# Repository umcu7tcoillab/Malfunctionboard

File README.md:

# Malfunctionboard

## About us
This design has been made by the coil-lab of the High Field MRI Group of the UMC Utrecht in the Netherlands, where we make hardware to support our researchers. We are part of a research group which means we feel the need to open up some of our designs to whomever can make use of it, to further the research of MRI applications.

## The design
This project contains a Malfunctionboard made for our 7T Philips Achieva MRI system. It has been tested inside the magnetic field of the 7T MRI. 

The Malfunctionboard is used to check the state of the PIN-diodes of the attachted coil. Between 1 and 3 diodes (0.4-2.6V) passes the test, otherwise the malfunctionline will not be pulled high.

The design and subsequent drawing has been done in Kicad 5.1.5.

## Download
Gerber and BOM production files for the latest _field tested_ version of the PCB can be found in the 'Releases' page, or by following [this link](https://github.com/umcu7tcoillab/Malfunctionboard/releases/latest). 
You can also make your own production files by downloading the Kicad project and generating them, but these are not guaranteed to have been field tested.

## Images
**3D Image**

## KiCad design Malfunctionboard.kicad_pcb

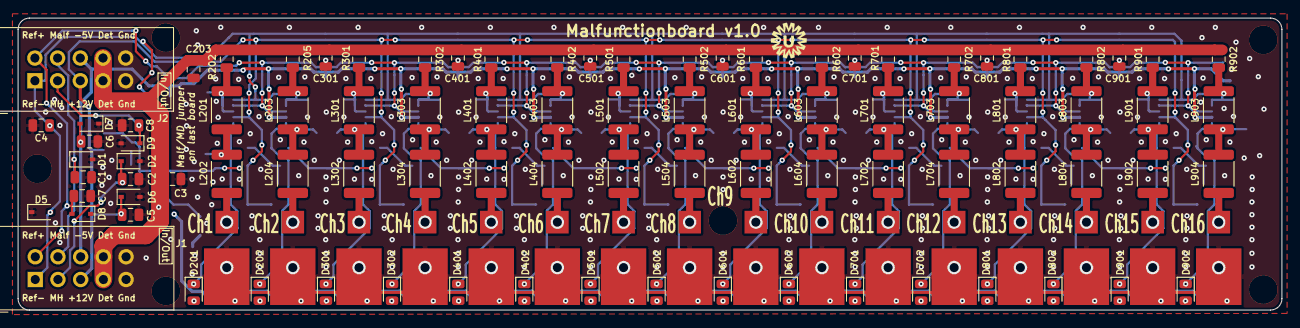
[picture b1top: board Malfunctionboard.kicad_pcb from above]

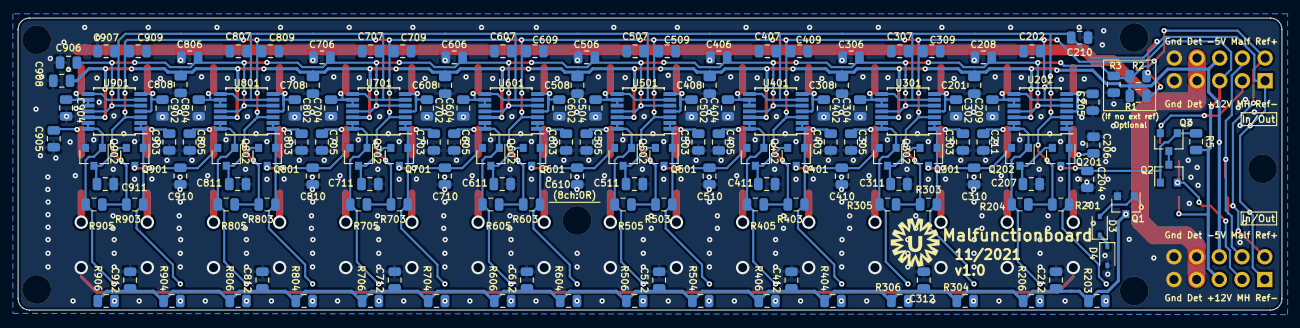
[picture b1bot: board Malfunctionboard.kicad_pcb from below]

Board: 2 copper layers, 141.4 x 32.7 mm, 265 parts (154 on the bottom side), 108 nets.

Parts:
C1, C2, C3, C4, C7, C8, C203, C204, C205, C206, C207, C208, C209, C210, C211, C301, C302, C303, C304, C305, C306, C307, C310, C311, C401, C402, C403, C404, C405, C406, C407, C410, C411, C501, C502, C503, C504, C505, C506, C507, C510, C511, C601, C602, C603, C604, C605, C606, C607, C610, C611, C701, C702, C703, C704, C705, C706, C707, C710, C711, C801, C802, C803, C804, C805, C806, C807, C810, C811, C901, C902, C903, C904, C905, C906, C907, C910, C911: 470pF; C_0805_2012Metric
C5, C6, C201, C202, C212, C308, C309, C312, C408, C409, C412, C508, C509, C512, C608, C609, C612, C708, C709, C712, C808, C809, C812, C908, C909, C912: 10n; C_0805_2012Metric
D1, D2, D6, D9: 15V; D_SOD-323
D3, D5, D7, D8: 5.4V; D_SOD-323
D4: 12V; D_SOD-323
D201, D202, D301, D302, D401, D402, D501, D502, D601, D602, D701, D702, D801, D802, D901, D902: LED; LED_0805_2012Metric
H1, H3, H4, H5, H6, H7: MH_Pad; MountingHole_3.2mm_M3_plated
J1, J2: In/out; IDC-Header_2x05_P2.54mm_Vertical
J201, J202, J301, J302, J401, J402, J501, J502, J601, J602, J701, J702, J801, J802, J901, J902: Conn_Coaxial; Solder straight thin coax cable
L201, L202, L203, L204, L301, L302, L303, L304, L401, L402, L403, L404, L501, L502, L503, L504, L601, L602, L603, L604, L701, L702, L703, L704, L801, L802, L803, L804, L901, L902, L903, L904: 1u; L_1812_4532Metric
Q1, Q2, Q3: RSC002P03T316; SOT-23
Q201, Q202, Q301, Q302, Q401, Q402, Q501, Q502, Q601, Q602, Q701, Q702, Q801, Q802, Q901, Q902: NTR5103NT1G; SOT-23
R1: R_Ref-; R_0805_2012Metric
R2: R_Ref; R_0805_2012Metric
R3: R_Ref+; R_0805_2012Metric
R5: 1k; R_0805_2012Metric
R201, R204, R303, R305, R403, R405, R503, R505, R603, R605, R703, R705, R803, R805, R903, R905: 100k; R_0805_2012Metric
R202, R205, R301, R302, R401, R402, R501, R502, R601, R602, R701, R702, R801, R802, R901, R902: 150R; R_0805_2012Metric
R203, R206, R304, R306, R404, R406, R504, R506, R604, R606, R704, R706, R804, R806, R904, R906: 10k; R_0805_2012Metric
SYM1: SYM_Magnet_Small; UMC_logo_small
U201, U301, U401, U501, U601, U701, U801, U901: LM339PW; TSSOP-14_4.4x5mm_P0.65mm

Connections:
+12V: C5.1, C202.2, C309.2, C409.2, C509.2, C609.2, C709.2, C809.2, C909.2, D6.1, J1.5, J2.5, R5.1, R201.1, R204.1, R303.1, R305.1, R403.1, R405.1, R503.1, R505.1, R603.1, R605.1, R703.1, R705.1, R803.1, R805.1, R903.1, R905.1, U201.3, U301.3, U401.3, U501.3, U601.3, U701.3, U801.3, U901.3
-5V: C6.1, C201.2, C308.2, C408.2, C508.2, C608.2, C708.2, C808.2, C908.2, D7.2, J1.6, J2.6, R1.1, U201.12, U301.12, U401.12, U501.12, U601.12, U701.12, U801.12, U901.12
/MH_1: C2.2, D2.1, J1.3, Q2.2
/MH_2: C8.2, D9.1, J2.3, Q3.2
/Malf: C1.2, D1.1, J1.4, J2.4
/Ref+: C7.2, C208.2, C306.2, C406.2, C506.2, C606.2, C706.2, C806.2, C906.2, D8.2, J1.2, J2.2, R2.2, R3.1, U201.5, U201.11, U301.5, U301.11, U401.5, U401.11, U501.5, U501.11, U601.5, U601.11, U701.5, U701.11, U801.5, U801.11, U901.5, U901.11
/Ref-: C4.2, C210.2, C307.2, C407.2, C507.2, C607.2, C707.2, C807.2, C907.2, D5.2, J1.1, J2.1, R1.2, R2.1, U201.6, U201.8, U301.6, U301.8, U401.6, U401.8, U501.6, U501.8, U601.6, U601.8, U701.6, U701.8, U801.6, U801.8, U901.6, U901.8
/V_detune: C3.2, C203.2, C301.2, C401.2, C501.2, C601.2, C701.2, C801.2, C901.2, D3.2, J1.7, J1.8, J2.7, J2.8, Q1.1, R202.1, R205.1, R301.1, R302.1, R401.1, R402.1, R501.1, R502.1, R601.1, R602.1, R701.1, R702.1, R801.1, R802.1, R901.1, R902.1
/sheet5DD8DCB3/LED_GND: C212.1, C312.1, C412.1, C512.1, C612.1, C712.1, C812.1, C912.1, Q1.3, R203.2, R206.2, R304.2, R306.2, R404.2, R406.2, R504.2, R506.2, R604.2, R606.2, R704.2, R706.2, R804.2, R806.2, R904.2, R906.2
/sheet5DD8DCB3/Malf: C310.2, Q202.2, Q301.3
/sheet5DD8DCB3/Malf_in: C204.2, Q2.1, Q3.1, Q201.3, R5.2
/sheet5DE59C6C/Malf: C410.2, Q302.2, Q401.3
/sheet5DF0CFC9/Malf: C510.2, Q402.2, Q501.3
/sheet5DF0CFCA/Malf: C610.2, Q502.2, Q601.3
/sheet5DF270F0/Malf: C710.2, Q602.2, Q701.3
/sheet5DF270F1/Malf: C810.2, Q702.2, Q801.3
/sheet5DF3552B/Malf: C910.2, Q802.2, Q901.3
GND: C1.1, C2.1, C3.1, C4.1, C5.2, C6.2, C7.1, C8.1, C201.1, C202.1, C203.1, C204.1, C205.1, C206.1, C207.2, C208.1, C209.1, C210.1, C211.1, C212.2, C301.1, C302.1, C303.1, C304.1, C305.1, C306.1, C307.1, C308.1, C309.1, C310.1, C311.2, C312.2, C401.1, C402.1, C403.1, C404.1, C405.1, C406.1, C407.1, C408.1, C409.1, C410.1, C411.2, C412.2, C501.1, C502.1, C503.1, C504.1, C505.1, C506.1, C507.1, C508.1, C509.1, C510.1, C511.2, C512.2, C601.1, C602.1, C603.1, C604.1, C605.1, C606.1, C607.1, C608.1, C609.1, C610.1, C611.2, C612.2, C701.1, C702.1, C703.1, C704.1, C705.1, C706.1, C707.1, C708.1, C709.1, C710.1, C711.2, C712.2, C801.1, C802.1, C803.1, C804.1, C805.1, C806.1, C807.1, C808.1, C809.1, C810.1, C811.2, C812.2, C901.1, C902.1, C903.1, C904.1, C905.1, C906.1, C907.1, C908.1, C909.1, C910.1, C911.2, C912.2, D1.2, D2.2, D4.2, D5.1, D6.2, D7.1, D8.1, D9.2, H1.1, H3.1, H4.1, H5.1, H6.1, H7.1, J1.9, J1.10, J2.9, J2.10, J201.2, J202.2, J301.2, J302.2, J401.2, J402.2, J501.2, J502.2, J601.2, J602.2, J701.2, J702.2, J801.2, J802.2, J901.2, J902.2, Q1.2, Q902.2, R3.2
unnamed: C205.2, L201.2, R202.2, U201.4, U201.7
unnamed: C206.2, L201.1, L202.2
unnamed: C207.1, Q201.2, Q202.3
unnamed: C209.2, L203.2, R205.2, U201.9, U201.10
unnamed: C211.2, L203.1, L204.2
unnamed: C302.2, L301.2, R301.2, U301.4, U301.7
unnamed: C303.2, L301.1, L302.2
unnamed: C304.2, L303.2, R302.2, U301.9, U301.10
unnamed: C305.2, L303.1, L304.2
unnamed: C311.1, Q301.2, Q302.3
unnamed: C402.2, L401.2, R401.2, U401.4, U401.7
unnamed: C403.2, L401.1, L402.2
unnamed: C404.2, L403.2, R402.2, U401.9, U401.10
unnamed: C405.2, L403.1, L404.2
unnamed: C411.1, Q401.2, Q402.3
unnamed: C502.2, L501.2, R501.2, U501.4, U501.7
unnamed: C503.2, L501.1, L502.2
unnamed: C504.2, L503.2, R502.2, U501.9, U501.10
unnamed: C505.2, L503.1, L504.2
unnamed: C511.1, Q501.2, Q502.3
unnamed: C602.2, L601.2, R601.2, U601.4, U601.7
unnamed: C603.2, L601.1, L602.2
unnamed: C604.2, L603.2, R602.2, U601.9, U601.10
unnamed: C605.2, L603.1, L604.2
unnamed: C611.1, Q601.2, Q602.3
unnamed: C702.2, L701.2, R701.2, U701.4, U701.7
unnamed: C703.2, L701.1, L702.2
unnamed: C704.2, L703.2, R702.2, U701.9, U701.10
unnamed: C705.2, L703.1, L704.2
unnamed: C711.1, Q701.2, Q702.3
unnamed: C802.2, L801.2, R801.2, U801.4, U801.7
unnamed: C803.2, L801.1, L802.2
unnamed: C804.2, L803.2, R802.2, U801.9, U801.10
unnamed: C805.2, L803.1, L804.2
unnamed: C811.1, Q801.2, Q802.3
unnamed: C902.2, L901.2, R901.2, U901.4, U901.7
unnamed: C903.2, L901.1, L902.2
unnamed: C904.2, L903.2, R902.2, U901.9, U901.10
unnamed: C905.2, L903.1, L904.2
unnamed: C911.1, Q901.2, Q902.3
unnamed: D3.1, D4.1
unnamed: D201.1, Q201.1, R201.2, U201.1, U201.2
unnamed: D201.2, R203.1
unnamed: D202.1, Q202.1, R204.2, U201.13, U201.14
unnamed: D202.2, R206.1
unnamed: D301.1, Q301.1, R303.2, U301.1, U301.2
unnamed: D301.2, R304.1
unnamed: D302.1, Q302.1, R305.2, U301.13, U301.14
unnamed: D302.2, R306.1
unnamed: D401.1, Q401.1, R403.2, U401.1, U401.2
unnamed: D401.2, R404.1
unnamed: D402.1, Q402.1, R405.2, U401.13, U401.14
unnamed: D402.2, R406.1
unnamed: D501.1, Q501.1, R503.2, U501.1, U501.2
unnamed: D501.2, R504.1
unnamed: D502.1, Q502.1, R505.2, U501.13, U501.14
unnamed: D502.2, R506.1
unnamed: D601.1, Q601.1, R603.2, U601.1, U601.2
unnamed: D601.2, R604.1
unnamed: D602.1, Q602.1, R605.2, U601.13, U601.14
unnamed: D602.2, R606.1
unnamed: D701.1, Q701.1, R703.2, U701.1, U701.2
unnamed: D701.2, R704.1
unnamed: D702.1, Q702.1, R705.2, U701.13, U701.14
unnamed: D702.2, R706.1
unnamed: D801.1, Q801.1, R803.2, U801.1, U801.2
unnamed: D801.2, R804.1
unnamed: D802.1, Q802.1, R805.2, U801.13, U801.14
unnamed: D802.2, R806.1
unnamed: D901.1, Q901.1, R903.2, U901.1, U901.2
unnamed: D901.2, R904.1
unnamed: D902.1, Q902.1, R905.2, U901.13, U901.14
unnamed: D902.2, R906.1
unnamed: J201.1, L202.1
unnamed: J202.1, L204.1
unnamed: J301.1, L302.1
unnamed: J302.1, L304.1
unnamed: J401.1, L402.1
unnamed: J402.1, L404.1
unnamed: J501.1, L502.1
unnamed: J502.1, L504.1
unnamed: J601.1, L602.1
unnamed: J602.1, L604.1
unnamed: J701.1, L702.1
unnamed: J702.1, L704.1
unnamed: J801.1, L802.1
unnamed: J802.1, L804.1
unnamed: J901.1, L902.1
unnamed: J902.1, L904.1
unnamed: Q2.3, Q3.3

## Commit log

2019-11-21 Changed: more robust malfunction check
2019-11-22 Finished main design
2019-11-22 Changed: design to accomodate quad comparator package. Added: all labels for the connectors
2019-11-22 Made first pcb sketch, but is too wide
2019-11-23 Finished main pcb design. Todo: move decouple C's to backside, move logic at connectors to back, better mounting hole position
2019-11-24 Finished v0.1
2019-11-25 Changed: started changing circuit between connectors
2019-11-25 changed: Added extra protection C's to v0.1
2019-11-27 Ready for ordering. Changed: some overlapping via's, moved mounting holes slightly and made them plated.
2019-12-11 Changed: small changes
2019-12-19 Changed: different annotations, small changes
2020-02-25 Added: Through holes in the coaxial pads, for use as interfacebox module; README, LICENSE.
2020-02-26 Changed: Removed unnecessary references in file
2020-02-26 Removed: unnecessary file
2020-03-05 Updated LICENSE
2020-03-12 Fixed: wrong pin layout for comparator
2020-03-18 Changed: Adjusted the in/out connectors for new driverboard (v0.3)
2020-03-18 Updated: date & version
2020-04-10 Changed: version number. Added: one missing track on comparator. Removed: resistor on internal malfunction
2020-04-24 Changed: fixed mistake in turning off LED's during +12v on detune.
2021-11-24 Changed: resistor and zener diode values.
2021-11-24 Updated to v1.0
2021-11-24 Updated version date
